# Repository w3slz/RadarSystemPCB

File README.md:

# Radar System PCB

## Instructions
Copy All Files to a Folder.  Run KiCad and Open Project by Selecting "Q2.Pro".

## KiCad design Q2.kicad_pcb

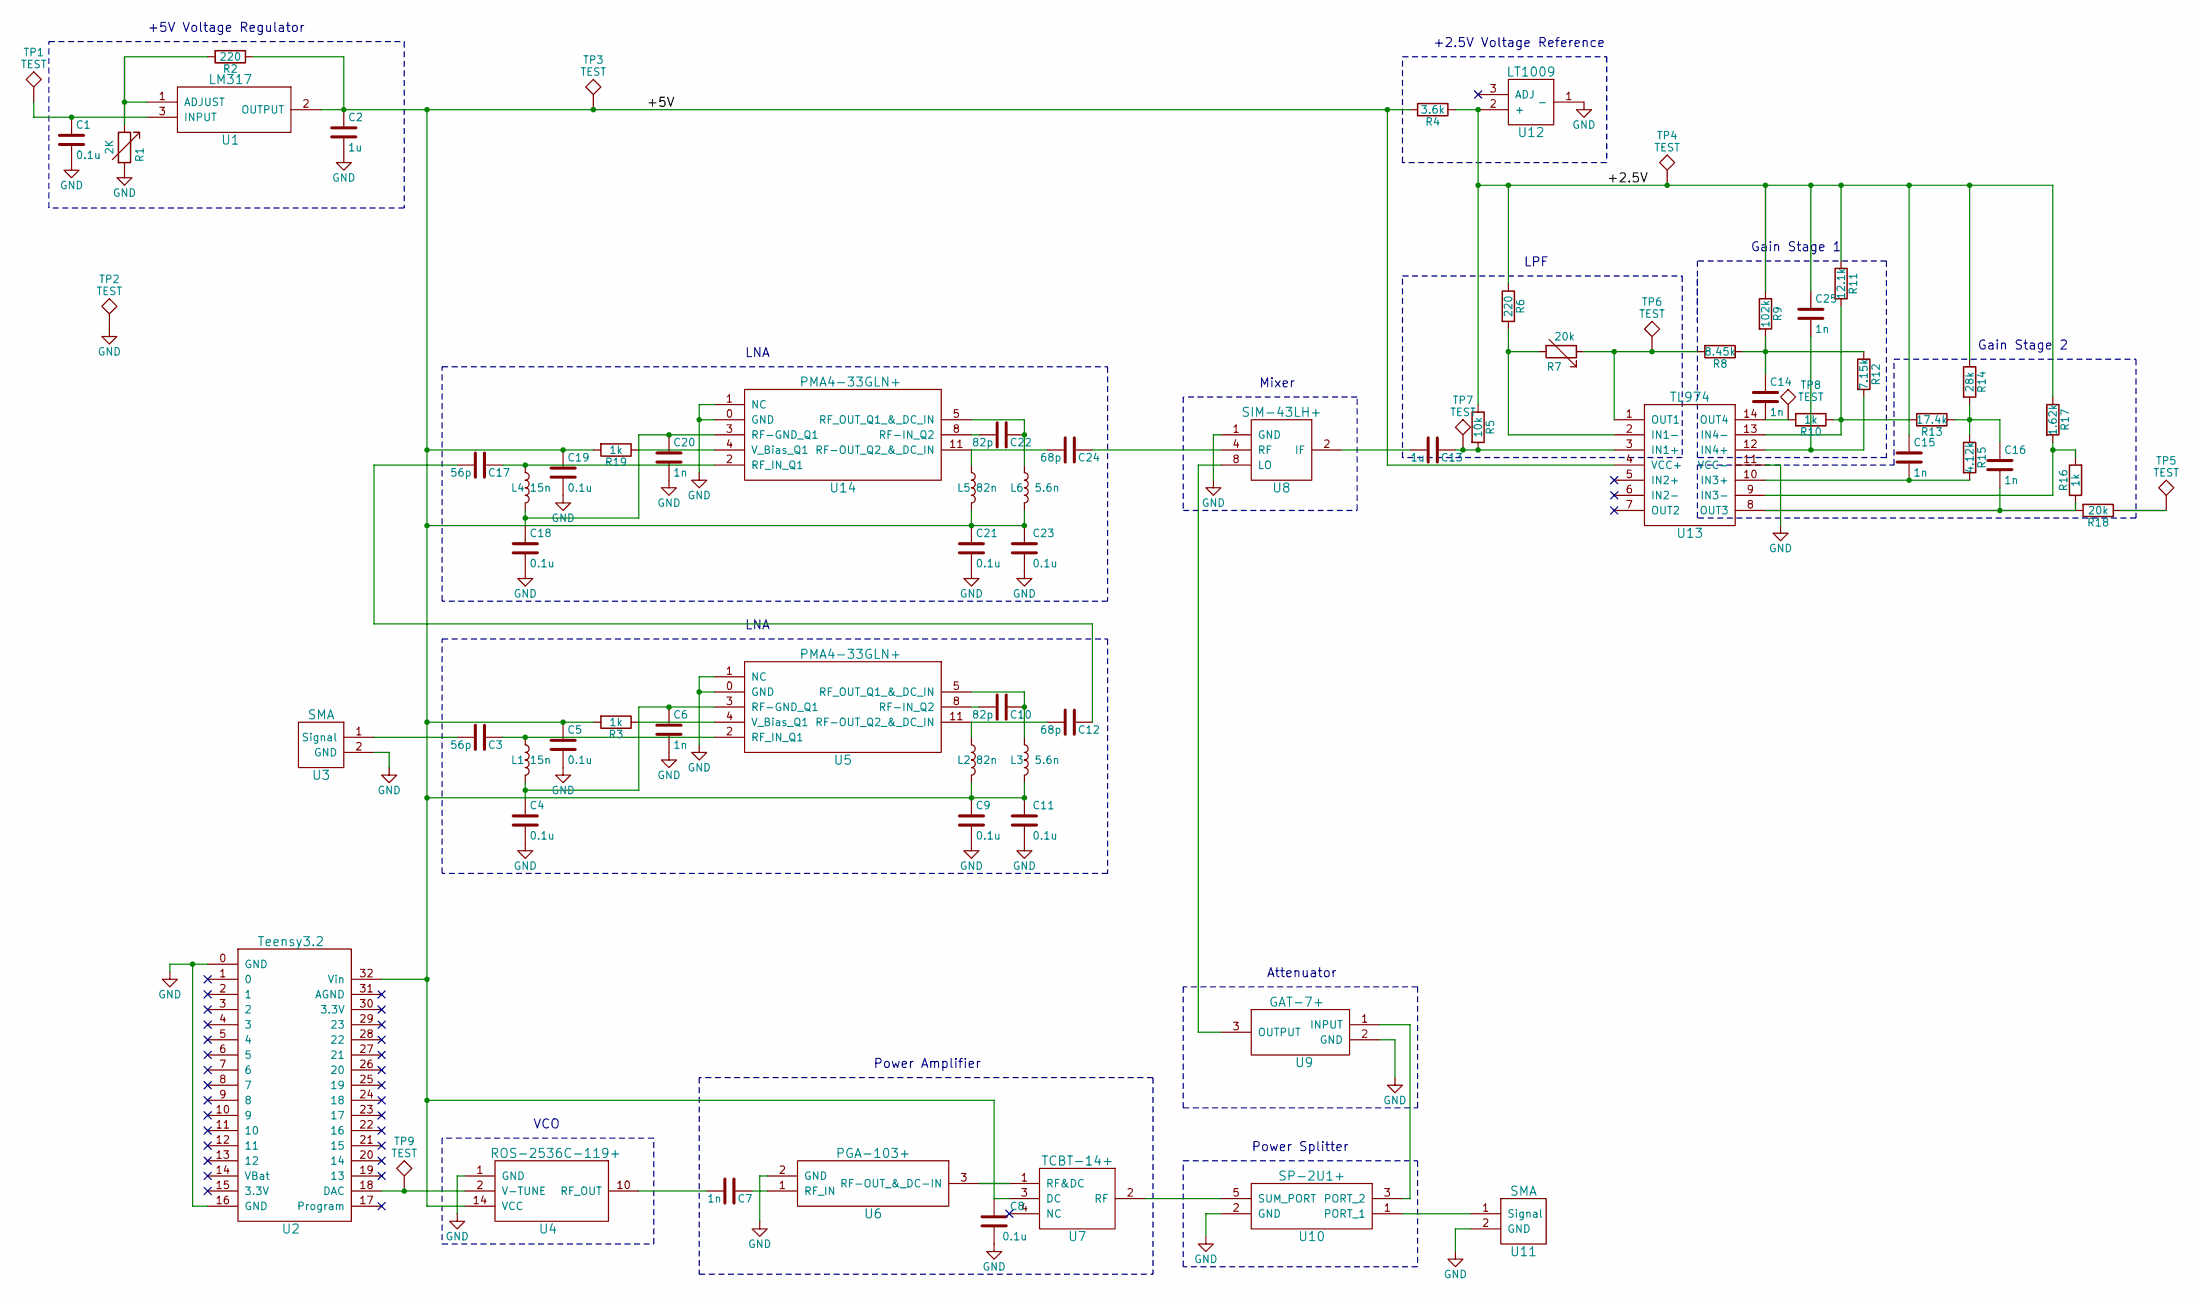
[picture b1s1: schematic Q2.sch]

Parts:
C1, C4, C5, C8, C9, C11, C18, C19, C21, C23: 0.1u; C_0805_HandSoldering
C2, C13: 1u; C_0805_HandSoldering
C3, C17: 56p; C_0805_HandSoldering
C6, C7, C14, C15, C16, C20, C25: 1n; C_0805_HandSoldering
C10, C22: 82p; C_0805_HandSoldering
C12, C24: 68p; C_0805_HandSoldering
L1, L4: 15n; L_0805_HandSoldering
L2, L5: 82n; L_0805_HandSoldering
L3, L6: 5.6n; L_0805_HandSoldering
R1: 2K; Potentiometer_Trimmer_Bourns_3296W
R2, R6: 220; R_0805_HandSoldering
R3, R10, R16, R19: 1k; R_0805_HandSoldering
R4: 3.6k; R_0805_HandSoldering
R5: 10k; R_0805_HandSoldering
R7: 20k; Potentiometer_Trimmer_Bourns_3296W
R8: 8.45k; R_0805_HandSoldering
R9: 102k; R_0805_HandSoldering
R11: 12.1k; R_0805_HandSoldering
R12: 7.15k; R_0805_HandSoldering
R13: 17.4k; R_0805_HandSoldering
R14: 28k; R_0805_HandSoldering
R15: 4.12k; R_0805_HandSoldering
R17: 1.62k; R_0805_HandSoldering
R18: 20k; R_0805_HandSoldering
TP1, TP2, TP3, TP4, TP5, TP6, TP7, TP8, TP9: TEST; PINTST
U1: LM317
U2: Teensy3.2
U3: SMA
U4: ROS-2536C-119+
U5, U14: PMA4-33GLN+
U6: PGA-103+
U7: TCBT-14+
U8: SIM-43LH+
U9: GAT-7+
U10: SP-2U1+
U11: SMA; SMA_Vertical
U12: LT1009
U13: TL974

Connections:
/+2.5V: C15.1, C25.1, R4.1, R5.1, R6.1, R9.1, R11.1, R14.1, R17.1, TP4.1, U12.2 (+)
/+5V: C2.1, C5.1, C8.1, C9.1, C11.1, C19.1, C21.1, C23.1, L2.2, L3.2, L5.2, L6.2, R2.1, R3.2, R4.2, R19.2, TP3.1, U1.2 (OUTPUT), U2.32 (Vin), U4.14 (VCC), U7.3 (DC), U13.4 (VCC+)
GND: C1.2, C2.2, C4.2, C5.2, C6.2, C8.2, C9.2, C11.2, C18.2, C19.2, C20.2, C21.2, C23.2, R1.2, TP2.1, U2.0 (GND), U2.16 (GND), U3.2 (GND), U4.1 (GND), U5.0 (GND), U5.1 (NC), U6.2 (GND), U8.1 (GND), U9.2 (GND), U10.2 (GND), U11.2 (GND), U12.1 (-), U13.11 (VCC-), U14.0 (GND), U14.1 (NC)
unnamed: C1.1, TP1.1, U1.3 (INPUT)
unnamed: C3.1, L1.1, U5.2 (RF_IN_Q1)
unnamed: C3.2, U3.1 (Signal)
unnamed: C4.1, C6.1, L1.2, U5.3 (RF-GND_Q1)
unnamed: C7.1, U6.1 (RF_IN)
unnamed: C7.2, U4.10 (RF_OUT)
unnamed: C10.1, L3.1, U5.5 (RF_OUT_Q1_&_DC_IN)
unnamed: C10.2, U5.8 (RF-IN_Q2)
unnamed: C12.1, C17.2
unnamed: C12.2, L2.1, U5.11 (RF-OUT_Q2_&_DC_IN)
unnamed: C13.1, R5.2, TP7.1, U13.3 (IN1+)
unnamed: C13.2, U8.2 (IF)
unnamed: C14.1, R8.1, R9.2, R12.1
unnamed: C14.2, R10.2, TP8.1, U13.14 (OUT4)
unnamed: C15.2, R15.2, U13.10 (IN3+)
unnamed: C16.1, R13.1, R14.2, R15.1
unnamed: C16.2, R16.1, R18.2, U13.8 (OUT3)
unnamed: C17.1, L4.1, U14.2 (RF_IN_Q1)
unnamed: C18.1, C20.1, L4.2, U14.3 (RF-GND_Q1)
unnamed: C22.1, L6.1, U14.5 (RF_OUT_Q1_&_DC_IN)
unnamed: C22.2, U14.8 (RF-IN_Q2)
unnamed: C24.1, U8.4 (RF)
unnamed: C24.2, L5.1, U14.11 (RF-OUT_Q2_&_DC_IN)
unnamed: C25.2, R12.2, U13.12 (IN4+)
unnamed: R1.1, R2.2, U1.1 (ADJUST)
unnamed: R3.1, U5.4 (V_Bias_Q1)
unnamed: R6.2, R7.2, U13.2 (IN1-)
unnamed: R7.1, R8.2, TP6.1, U13.1 (OUT1)
unnamed: R10.1, R11.2, R13.2, U13.13 (IN4-)
unnamed: R16.2, R17.2, U13.9 (IN3-)
unnamed: R18.1, TP5.1
unnamed: R19.1, U14.4 (V_Bias_Q1)
unnamed: TP9.1, U2.18 (DAC), U4.2 (V-TUNE)
unnamed: U6.3 (RF-OUT_&_DC-IN), U7.1 (RF&DC)
unnamed: U8.8 (LO), U9.3 (OUTPUT)
unnamed: U10.1 (PORT_1), U11.1 (Signal)
unnamed: U9.1 (INPUT), U10.3 (PORT_2)
unnamed: U7.2 (RF), U10.5 (SUM_PORT)

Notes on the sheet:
+5V Voltage Regulator
+2.5V Voltage Reference
LPF
Gain Stage 1
Gain Stage 2
VCO
Power Amplifier
Power Splitter
LNA
Attenuator
Mixer

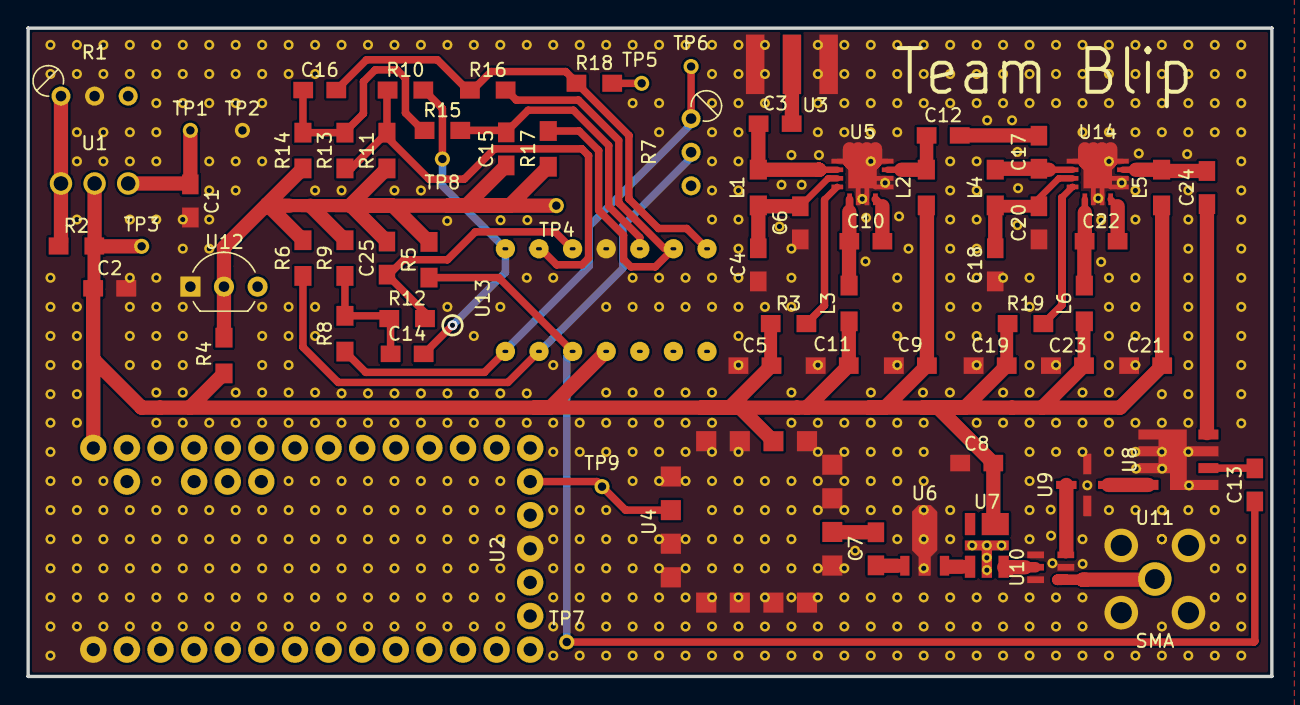
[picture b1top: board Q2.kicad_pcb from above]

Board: 2 copper layers, 94.0 x 49.0 mm, 73 parts (0 on the bottom side), 41 nets.

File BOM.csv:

Component,Description,Part,References,Value,Footprint,Quantity Per PCB,Datasheet
1,Unpolarized capacitor,C,C1 C4 C5 C8 C9 C11 C18 C19 C21 C23,0.1u,C_0805_HandSoldering,10,
2,Unpolarized capacitor,C,C6 C7 C14 C15 C16 C20 C25,1n,C_0805_HandSoldering,7,
3,Unpolarized capacitor,C,C2 C13,1u,C_0805_HandSoldering,2,
4,Unpolarized capacitor,C,C3 C17,56p,C_0805_HandSoldering,2,
5,Unpolarized capacitor,C,C12 C24,68p,C_0805_HandSoldering,2,
6,Unpolarized capacitor,C,C10 C22,82p,C_0805_HandSoldering,2,
7,Inductor,L,L1 L4,15n,L_0805_HandSoldering,2,
8,Inductor,L,L3 L6,5.6n,L_0805_HandSoldering,2,
9,Inductor,L,L2 L5,82n,L_0805_HandSoldering,2,
10,Resistor,R,R17,1.62k,R_0805_HandSoldering,1,
11,Resistor,R,R9,102k,R_0805_HandSoldering,1,
12,Resistor,R,R5,10k,R_0805_HandSoldering,1,
13,Resistor,R,R11,12.1k,R_0805_HandSoldering,1,
14,Resistor,R,R13,17.4k,R_0805_HandSoldering,1,
15,Resistor,R,R3 R10 R16 R19,1k,R_0805_HandSoldering,4,
16,Resistor,R,R18,20k,R_0805_HandSoldering,1,
17,variable Resistor (Rheostat),R_Variable,R7,20k,Potentiometer_Trimmer_Bourns_3296W,1,
18,Resistor,R,R2 R6,220,R_0805_HandSoldering,2,
19,Resistor,R,R14,28k,R_0805_HandSoldering,1,
20,variable Resistor (Rheostat),R_Variable,R1,2K,Potentiometer_Trimmer_Bourns_3296W,1,
21,Resistor,R,R4,3.6k,R_0805_HandSoldering,1,
22,Resistor,R,R15,4.12k,R_0805_HandSoldering,1,
23,Resistor,R,R12,7.15k,R_0805_HandSoldering,1,
24,Resistor,R,R8,8.45k,R_0805_HandSoldering,1,
25,,GAT-7+,U9,GAT-7+,GAT-7+,1,
26,,LM317,U1,LM317,LM317,1,
27,,LT1009,U12,LT1009,LT1009,1,
28,,PGA-103+,U6,PGA-103+,PGA-103+,1,
29,,PMA4-33GLN+,U5 U14,PMA4-33GLN+,PMA4-33GLN+,2,
30,,ROS-2536C-119+,U4,ROS-2536C-119+,ROS-2536C-119+,1,
31,,SIM-43LH+,U8,SIM-43LH+,SIM-43LH+,1,
32,,SMA,U11,SMA,SMA_Vertical,1,
33,,SMA,U3,SMA,SMA,1,
34,,SP-2U1+,U10,SP-2U1+,SP-2U1+,1,
35,,TCBT-14+,U7,TCBT-14+,TCBT-14+,1,
36,,TL974,U13,TL974,TL974,1,
37,,Teensy3.2,U2,Teensy3.2,Teensy3.2,1,
,,,,,,,
,,,,,,,
,,,,,,,
,,,,,,,
,,,,,,,
Component Groups:,37,,,,,,
Component Count:,64,,,,,,
Fitted Components:,64,,,,,,
Number of PCBs:,1,,,,,,
Total components:,64,,,,,,
Schematic Version:,,,,,,,
Schematic Date:,,,,,,,
BoM Date:,2/11/2018 18:59,,,,,,
Schematic Source:,C:/Users/Wesley/Desktop/EEC 134/Q2/Q2.sch,,,,,,
KiCad Version:,Eeschema 4.0.7,,,,,,

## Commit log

2018-02-08 PCB Fix + DFM Report + PCB Width Calculation
    Fixed Track Width
2018-02-08 Update
    Fix Ground Connection Issues
    Cleaned Up Ground Connection
    Fixed Via Ground Connection Issues
2018-02-09 Update
    Fixed Missing LNA
2018-02-09 Update
    Fixed SMA Edge
2018-02-09 Update
    Fixed LNA Connection
